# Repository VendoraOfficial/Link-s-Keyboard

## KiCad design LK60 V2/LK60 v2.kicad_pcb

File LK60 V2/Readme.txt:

LK60 V2 is a 60% keyboard with arduino pro micro as the microcontroller and use 2 mounting hole.

If u r wondering where is the v1. The project was gone into ashes, cause of my laptop got formated :')

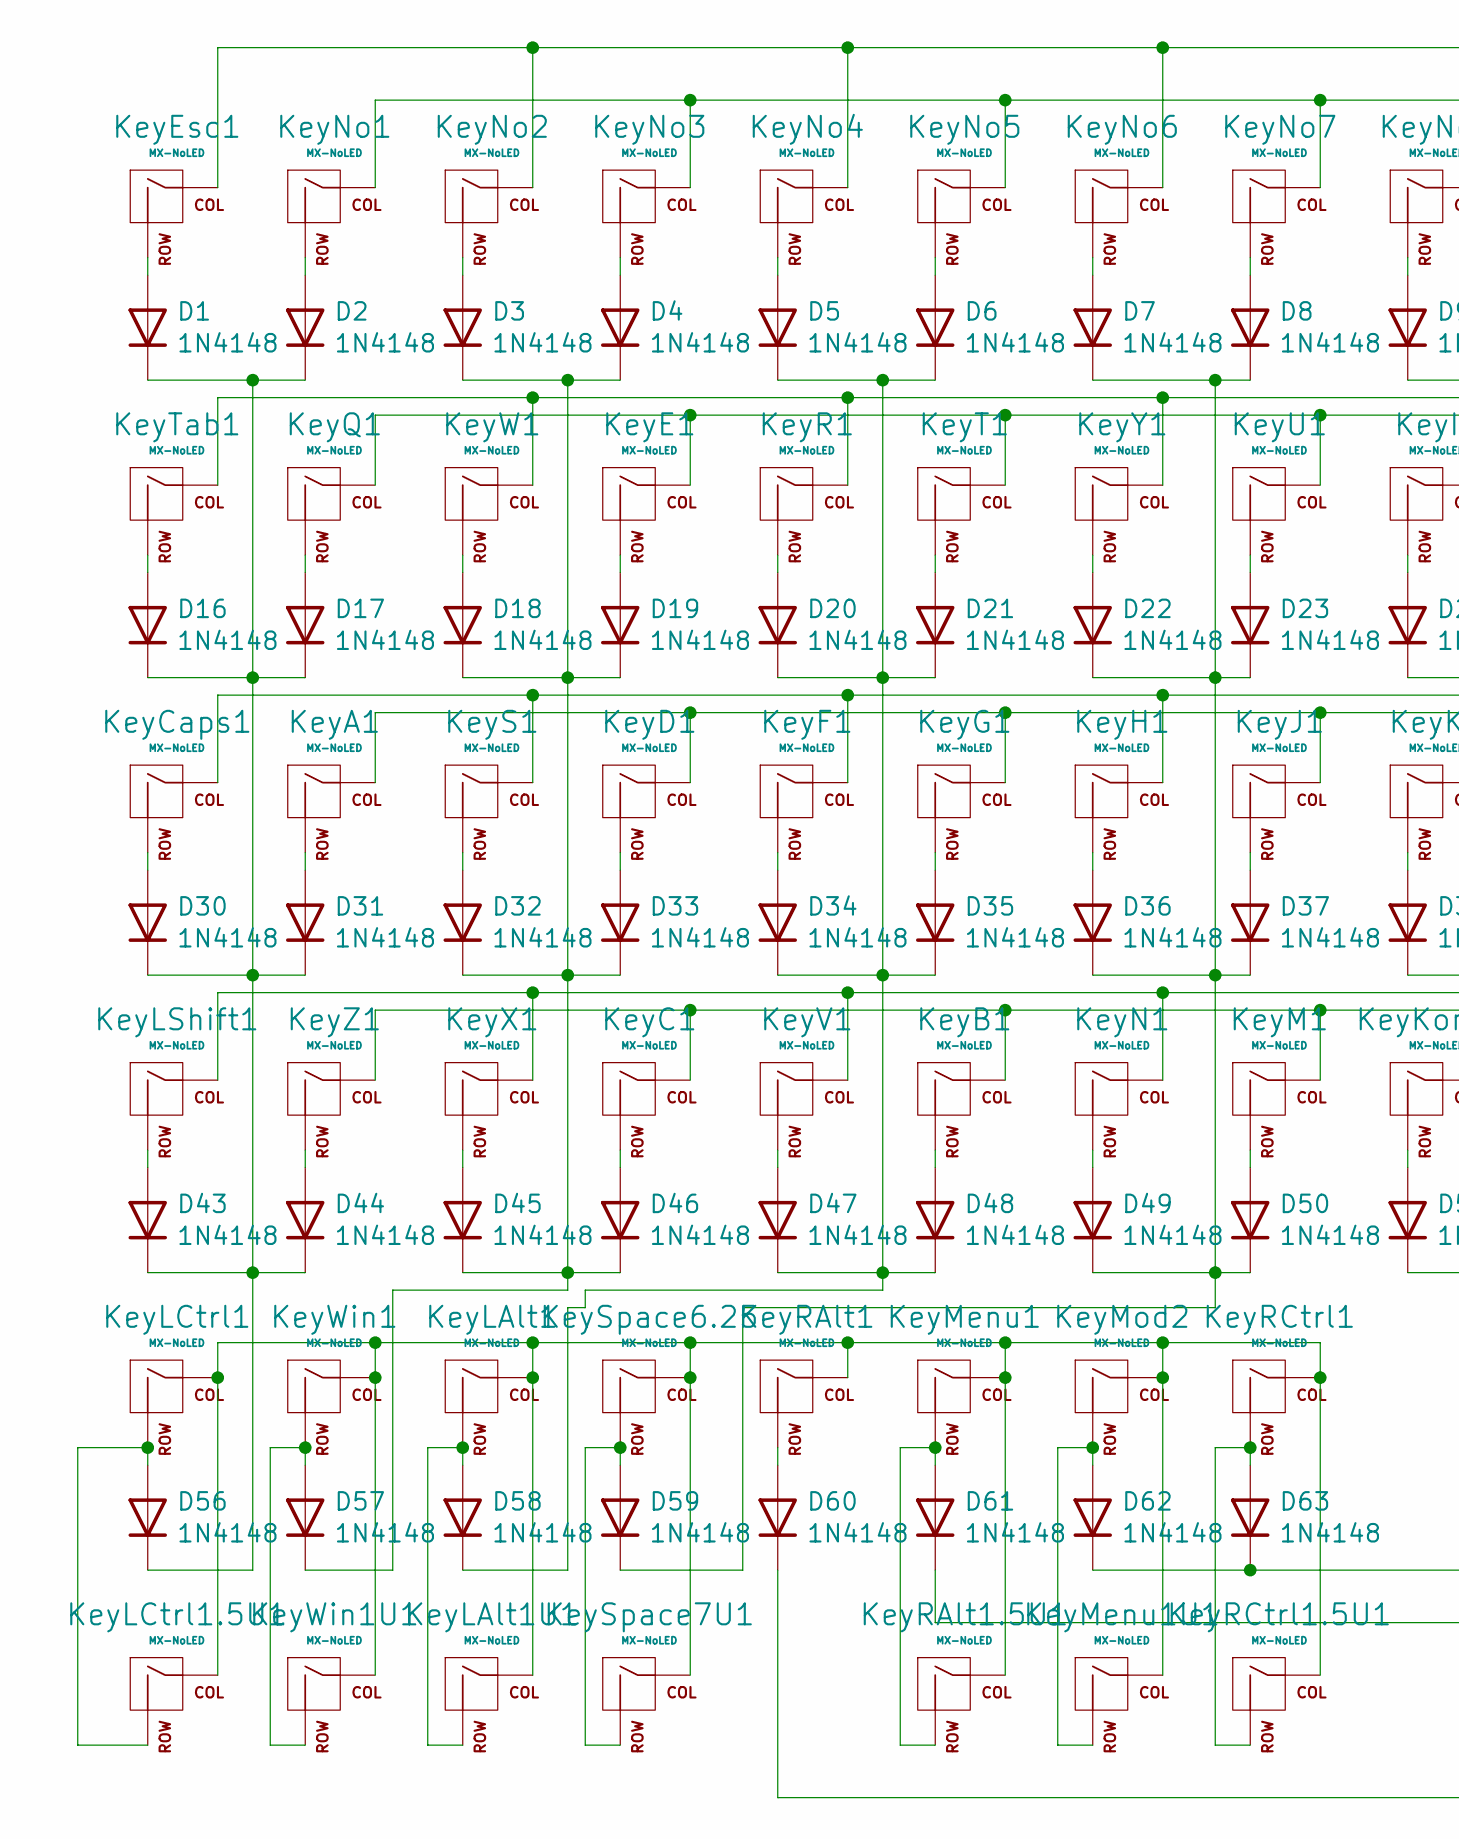
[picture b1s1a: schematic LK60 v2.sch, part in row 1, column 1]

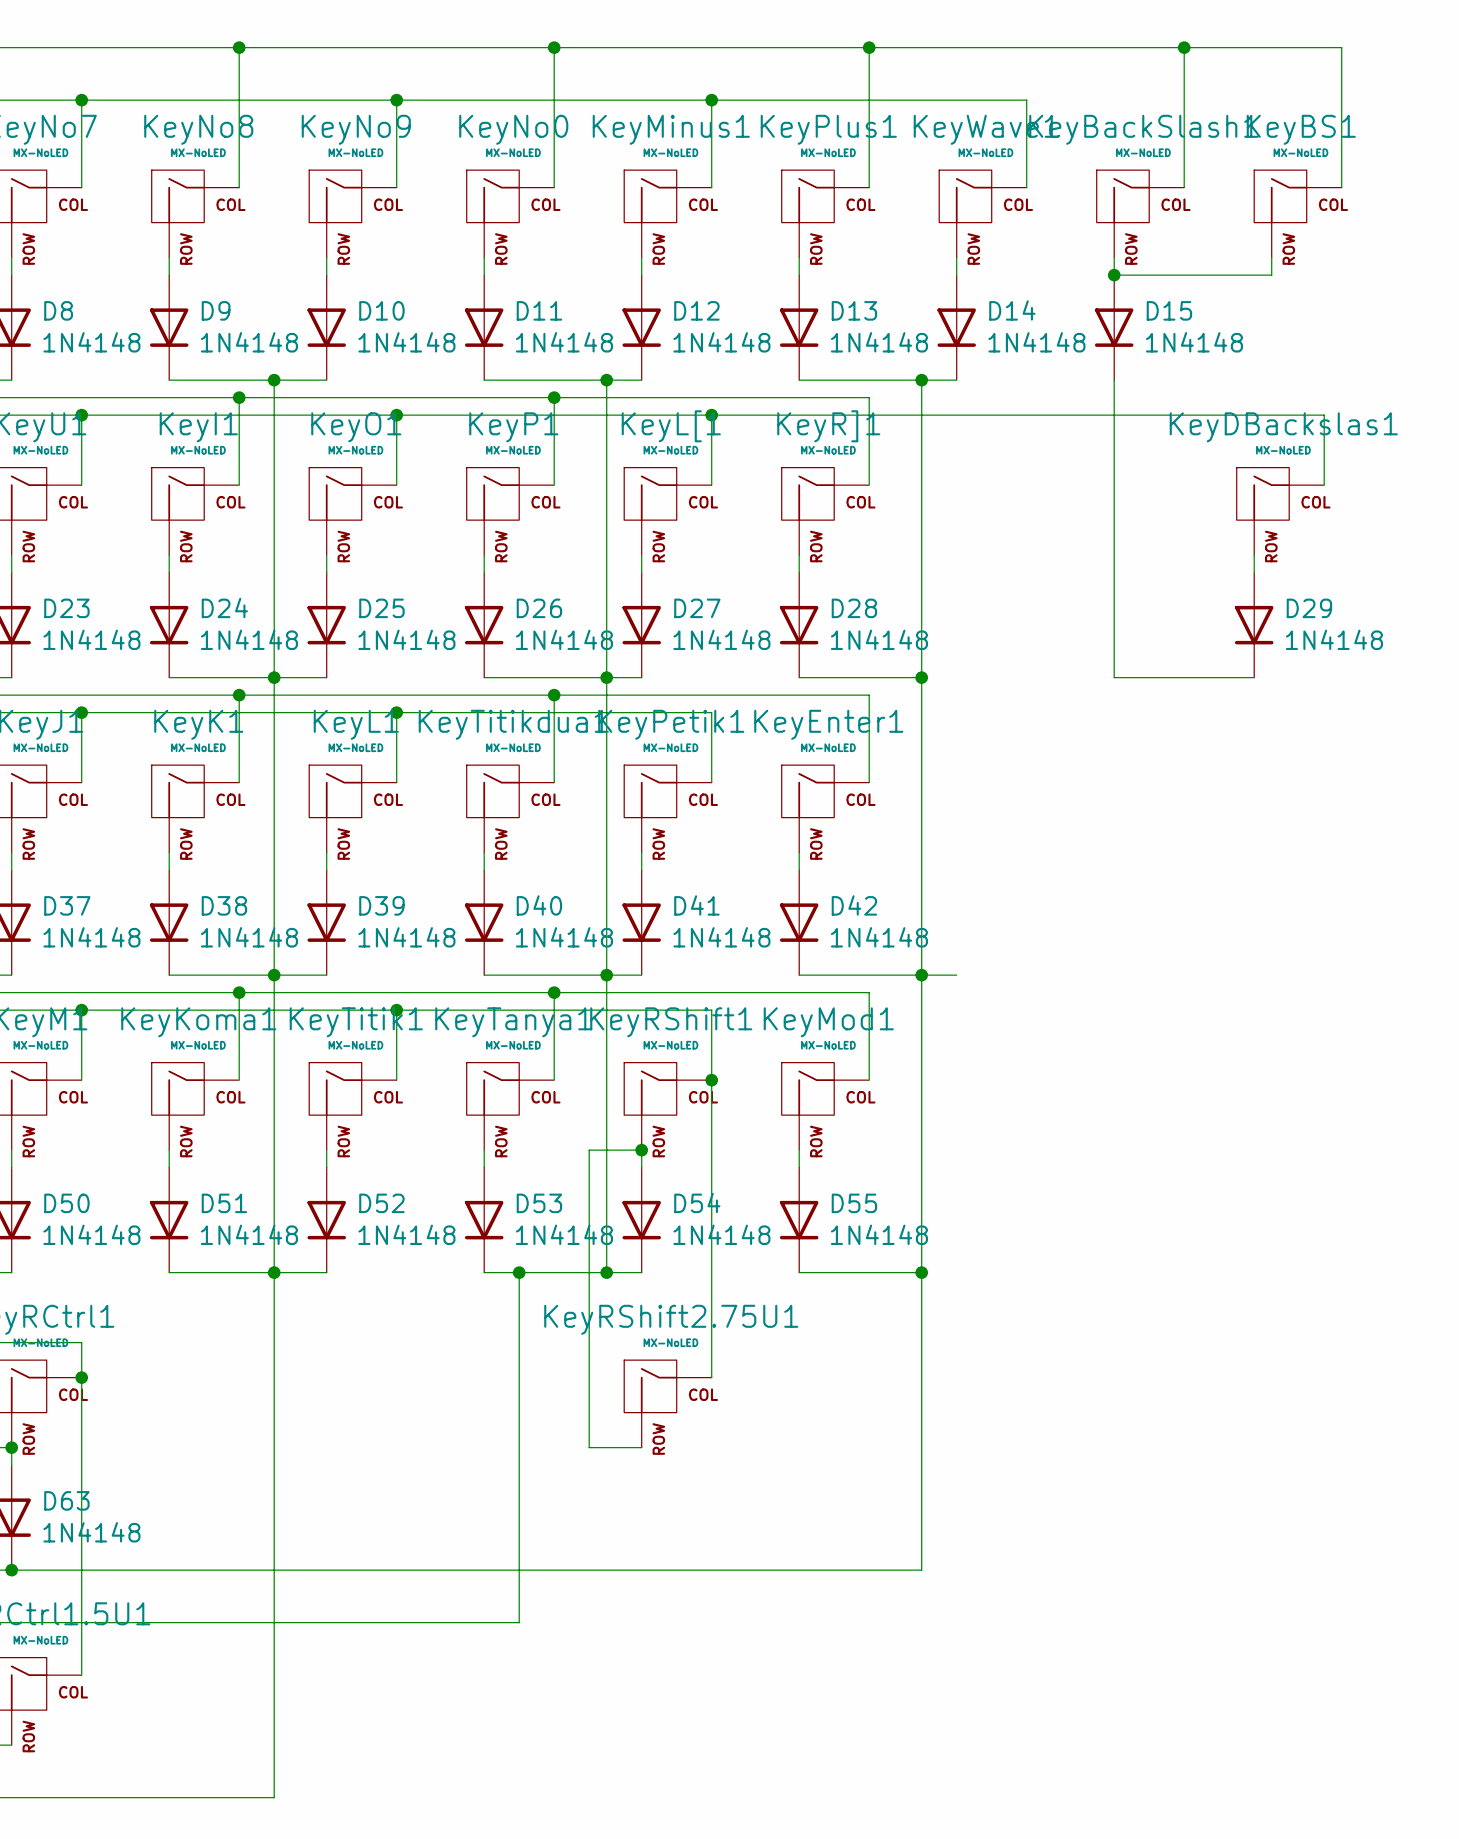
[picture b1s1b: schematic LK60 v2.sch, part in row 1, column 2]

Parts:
D1, D2, D3, D4, D5, D6, D7, D8, D9, D10, D11, D12, D13, D14, D15, D16, D17, D18, D19, D20, D21, D22, D23, D24, D25, D26, D27, D28, D29, D30, D31, D32, D33, D34, D35, D36, D37, D38, D39, D40, D41, D42, D43, D44, D45, D46, D47, D48, D49, D50, D51, D52, D53, D54, D55, D56, D57, D58, D59, D60, D61, D62, D63: 1N4148; D_DO-35_SOD27_P7.62mm_Horizontal
KeyA1: MX-NoLED; MXOnly-1U-NoLED
KeyB1: MX-NoLED; MXOnly-1U-NoLED
KeyBS1: MX-NoLED; MXOnly-2U-NoLED
KeyBackSlash1: MX-NoLED; MXOnly-1U-NoLED
KeyC1: MX-NoLED; MXOnly-1U-NoLED
KeyCaps1: MX-NoLED; MXOnly-1.75U-NoLED
KeyD1: MX-NoLED; MXOnly-1U-NoLED
KeyDBackslas1: MX-NoLED; MXOnly-1.5U-NoLED
KeyE1: MX-NoLED; MXOnly-1U-NoLED
KeyEnter1: MX-NoLED; MXOnly-2.25U-ReversedStabilizers-NoLED
KeyEsc1: MX-NoLED; MXOnly-1U-NoLED
KeyF1: MX-NoLED; MXOnly-1U-NoLED
KeyG1: MX-NoLED; MXOnly-1U-NoLED
KeyH1: MX-NoLED; MXOnly-1U-NoLED
KeyI1: MX-NoLED; MXOnly-1U-NoLED
KeyJ1: MX-NoLED; MXOnly-1U-NoLED
KeyK1: MX-NoLED; MXOnly-1U-NoLED
KeyKoma1: MX-NoLED; MXOnly-1U-NoLED
KeyL1: MX-NoLED; MXOnly-1U-NoLED
KeyLAlt1: MX-NoLED; MXOnly-1.25U-NoLED
KeyLAlt1U1: MX-NoLED; MXOnly-1.5U-NoLED
KeyLCtrl1: MX-NoLED; MXOnly-1.25U-NoLED
KeyLCtrl1.5U1: MX-NoLED; MXOnly-1.5U-NoLED
KeyLShift1: MX-NoLED; MXOnly-2.25U-NoLED
KeyL[1: MX-NoLED; MXOnly-1U-NoLED
KeyM1: MX-NoLED; MXOnly-1U-NoLED
KeyMenu1: MX-NoLED; MXOnly-1.25U-NoLED
KeyMenu1U1: MX-NoLED; MXOnly-1U-NoLED
KeyMinus1: MX-NoLED; MXOnly-1U-NoLED
KeyMod1: MX-NoLED; MXOnly-1U-NoLED
KeyMod2: MX-NoLED; MXOnly-1.25U-NoLED
KeyN1: MX-NoLED; MXOnly-1U-NoLED
KeyNo0, KeyNo1, KeyNo2, KeyNo3, KeyNo4, KeyNo5, KeyNo6, KeyNo7, KeyNo8, KeyNo9: MX-NoLED; MXOnly-1U-NoLED
KeyO1: MX-NoLED; MXOnly-1U-NoLED
KeyP1: MX-NoLED; MXOnly-1U-NoLED
KeyPetik1: MX-NoLED; MXOnly-1U-NoLED
KeyPlus1: MX-NoLED; MXOnly-1U-NoLED
KeyQ1: MX-NoLED; MXOnly-1U-NoLED
KeyR1: MX-NoLED; MXOnly-1U-NoLED
KeyRAlt1: MX-NoLED; MXOnly-1.25U-NoLED
KeyRAlt1.5U1: MX-NoLED; MXOnly-1.5U-NoLED
KeyRCtrl1: MX-NoLED; MXOnly-1.25U-NoLED
KeyRCtrl1.5U1: MX-NoLED; MXOnly-1.5U-NoLED
KeyRShift1: MX-NoLED; MXOnly-1.75U-NoLED
KeyRShift2.75U1: MX-NoLED; MXOnly-2.75U-NoLED
KeyR]1: MX-NoLED; MXOnly-1U-NoLED
KeyS1: MX-NoLED; MXOnly-1U-NoLED
KeySpace6.25: MX-NoLED; MXOnly-6.25U-ReversedStabilizers-NoLED
KeySpace7U1: MX-NoLED; MXOnly-7U-ReversedStabilizers-NoLED
KeyT1: MX-NoLED; MXOnly-1U-NoLED
KeyTab1: MX-NoLED; MXOnly-1.5U-NoLED
KeyTanya1: MX-NoLED; MXOnly-1U-NoLED
KeyTitik1: MX-NoLED; MXOnly-1U-NoLED
KeyTitikdua1: MX-NoLED; MXOnly-1U-NoLED
KeyU1: MX-NoLED; MXOnly-1U-NoLED
KeyV1: MX-NoLED; MXOnly-1U-NoLED
KeyW1: MX-NoLED; MXOnly-1U-NoLED
KeyWave1: MX-NoLED; MXOnly-1U-NoLED
KeyWin1: MX-NoLED; MXOnly-1.25U-NoLED
KeyWin1U1: MX-NoLED; MXOnly-1U-NoLED
KeyX1: MX-NoLED; MXOnly-1U-NoLED
KeyY1: MX-NoLED; MXOnly-1U-NoLED
KeyZ1: MX-NoLED; MXOnly-1U-NoLED

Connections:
Col0: KeyBS1.1 (COL), KeyBackSlash1.1 (COL), KeyEsc1.1 (COL), KeyNo0.1 (COL), KeyNo2.1 (COL), KeyNo4.1 (COL), KeyNo6.1 (COL), KeyNo8.1 (COL), KeyPlus1.1 (COL); also elsewhere on the board
Col1: KeyMinus1.1 (COL), KeyNo1.1 (COL), KeyNo3.1 (COL), KeyNo5.1 (COL), KeyNo7.1 (COL), KeyNo9.1 (COL), KeyWave1.1 (COL); also elsewhere on the board
Col2: KeyI1.1 (COL), KeyP1.1 (COL), KeyR1.1 (COL), KeyR]1.1 (COL), KeyTab1.1 (COL), KeyW1.1 (COL), KeyY1.1 (COL); also elsewhere on the board
Col3: KeyDBackslas1.1 (COL), KeyE1.1 (COL), KeyL[1.1 (COL), KeyO1.1 (COL), KeyQ1.1 (COL), KeyT1.1 (COL), KeyU1.1 (COL); also elsewhere on the board
Col4: KeyCaps1.1 (COL), KeyEnter1.1 (COL), KeyF1.1 (COL), KeyH1.1 (COL), KeyK1.1 (COL), KeyS1.1 (COL), KeyTitikdua1.1 (COL); also elsewhere on the board
Col5: KeyA1.1 (COL), KeyD1.1 (COL), KeyG1.1 (COL), KeyJ1.1 (COL), KeyL1.1 (COL), KeyPetik1.1 (COL); also elsewhere on the board
Col6: KeyKoma1.1 (COL), KeyLShift1.1 (COL), KeyMod1.1 (COL), KeyN1.1 (COL), KeyTanya1.1 (COL), KeyV1.1 (COL), KeyX1.1 (COL); also elsewhere on the board
Col7: KeyB1.1 (COL), KeyC1.1 (COL), KeyM1.1 (COL), KeyRShift1.1 (COL), KeyRShift2.75U1.1 (COL), KeyTitik1.1 (COL), KeyZ1.1 (COL); also elsewhere on the board
Col8: KeyLAlt1.1 (COL), KeyLAlt1U1.1 (COL), KeyLCtrl1.1 (COL), KeyLCtrl1.5U1.1 (COL), KeyMenu1.1 (COL), KeyMenu1U1.1 (COL), KeyMod2.1 (COL), KeyRAlt1.1 (COL), KeyRAlt1.5U1.1 (COL), KeyRCtrl1.1 (COL), KeyRCtrl1.5U1.1 (COL), KeySpace6.25.1 (COL), KeySpace7U1.1 (COL), KeyWin1.1 (COL), KeyWin1U1.1 (COL); also elsewhere on the board
unnamed: D1.2 (A), KeyEsc1.2 (ROW)
unnamed: D2.2 (A), KeyNo1.2 (ROW)
unnamed: D3.2 (A), KeyNo2.2 (ROW)
unnamed: D4.2 (A), KeyNo3.2 (ROW)
unnamed: D5.2 (A), KeyNo4.2 (ROW)
unnamed: D6.2 (A), KeyNo5.2 (ROW)
unnamed: D7.2 (A), KeyNo6.2 (ROW)
unnamed: D8.2 (A), KeyNo7.2 (ROW)
unnamed: D9.2 (A), KeyNo8.2 (ROW)
unnamed: D10.2 (A), KeyNo9.2 (ROW)
unnamed: D11.2 (A), KeyNo0.2 (ROW)
unnamed: D12.2 (A), KeyMinus1.2 (ROW)
unnamed: D13.2 (A), KeyPlus1.2 (ROW)
unnamed: D14.2 (A), KeyWave1.2 (ROW)
unnamed: D15.2 (A), KeyBS1.2 (ROW), KeyBackSlash1.2 (ROW)
unnamed: D16.2 (A), KeyTab1.2 (ROW)
unnamed: D17.2 (A), KeyQ1.2 (ROW)
unnamed: D18.2 (A), KeyW1.2 (ROW)
unnamed: D19.2 (A), KeyE1.2 (ROW)
unnamed: D20.2 (A), KeyR1.2 (ROW)
unnamed: D21.2 (A), KeyT1.2 (ROW)
unnamed: D22.2 (A), KeyY1.2 (ROW)
unnamed: D23.2 (A), KeyU1.2 (ROW)
unnamed: D24.2 (A), KeyI1.2 (ROW)
unnamed: D25.2 (A), KeyO1.2 (ROW)
unnamed: D26.2 (A), KeyP1.2 (ROW)
unnamed: D27.2 (A), KeyL[1.2 (ROW)
unnamed: D28.2 (A), KeyR]1.2 (ROW)
unnamed: D29.2 (A), KeyDBackslas1.2 (ROW)
unnamed: D30.2 (A), KeyCaps1.2 (ROW)
unnamed: D31.2 (A), KeyA1.2 (ROW)
unnamed: D32.2 (A), KeyS1.2 (ROW)
unnamed: D33.2 (A), KeyD1.2 (ROW)
unnamed: D34.2 (A), KeyF1.2 (ROW)
unnamed: D35.2 (A), KeyG1.2 (ROW)
unnamed: D36.2 (A), KeyH1.2 (ROW)
unnamed: D37.2 (A), KeyJ1.2 (ROW)
unnamed: D38.2 (A), KeyK1.2 (ROW)
unnamed: D39.2 (A), KeyL1.2 (ROW)
unnamed: D40.2 (A), KeyTitikdua1.2 (ROW)
unnamed: D41.2 (A), KeyPetik1.2 (ROW)
unnamed: D42.2 (A), KeyEnter1.2 (ROW)
unnamed: D43.2 (A), KeyLShift1.2 (ROW)
unnamed: D44.2 (A), KeyZ1.2 (ROW)
unnamed: D45.2 (A), KeyX1.2 (ROW)
unnamed: D46.2 (A), KeyC1.2 (ROW)
unnamed: D47.2 (A), KeyV1.2 (ROW)
unnamed: D48.2 (A), KeyB1.2 (ROW)
unnamed: D49.2 (A), KeyN1.2 (ROW)
unnamed: D50.2 (A), KeyM1.2 (ROW)
unnamed: D51.2 (A), KeyKoma1.2 (ROW)
unnamed: D52.2 (A), KeyTitik1.2 (ROW)
unnamed: D53.2 (A), KeyTanya1.2 (ROW)
unnamed: D54.2 (A), KeyRShift1.2 (ROW), KeyRShift2.75U1.2 (ROW)
unnamed: D55.2 (A), KeyMod1.2 (ROW)
unnamed: D56.2 (A), KeyLCtrl1.2 (ROW), KeyLCtrl1.5U1.2 (ROW)
unnamed: D57.2 (A), KeyWin1.2 (ROW), KeyWin1U1.2 (ROW)
unnamed: D58.2 (A), KeyLAlt1.2 (ROW), KeyLAlt1U1.2 (ROW)
unnamed: D59.2 (A), KeySpace6.25.2 (ROW), KeySpace7U1.2 (ROW)
unnamed: D60.2 (A), KeyRAlt1.2 (ROW)
unnamed: D61.2 (A), KeyMenu1.2 (ROW), KeyRAlt1.5U1.2 (ROW)
unnamed: D62.2 (A), KeyMenu1U1.2 (ROW), KeyMod2.2 (ROW)
unnamed: D63.2 (A), KeyRCtrl1.2 (ROW), KeyRCtrl1.5U1.2 (ROW)
Row0: D1.1 (K), D2.1 (K), D16.1 (K), D17.1 (K), D30.1 (K), D31.1 (K), D43.1 (K), D44.1 (K), D56.1 (K); also elsewhere on the board
Row1: D3.1 (K), D4.1 (K), D18.1 (K), D19.1 (K), D32.1 (K), D33.1 (K), D45.1 (K), D46.1 (K), D57.1 (K); also elsewhere on the board
Row2: D5.1 (K), D6.1 (K), D20.1 (K), D21.1 (K), D34.1 (K), D35.1 (K), D47.1 (K), D48.1 (K), D58.1 (K); also elsewhere on the board
Row3: D7.1 (K), D8.1 (K), D22.1 (K), D23.1 (K), D36.1 (K), D37.1 (K), D49.1 (K), D50.1 (K), D59.1 (K); also elsewhere on the board
Row4: D9.1 (K), D10.1 (K), D24.1 (K), D25.1 (K), D38.1 (K), D39.1 (K), D51.1 (K), D52.1 (K), D60.1 (K); also elsewhere on the board
Row5: D11.1 (K), D12.1 (K), D26.1 (K), D27.1 (K), D40.1 (K), D41.1 (K), D53.1 (K), D54.1 (K), D61.1 (K); also elsewhere on the board
Row6: D13.1 (K), D14.1 (K), D28.1 (K), D42.1 (K), D55.1 (K), D62.1 (K), D63.1 (K); also elsewhere on the board
Row7: D15.1 (K), D29.1 (K); also elsewhere on the board

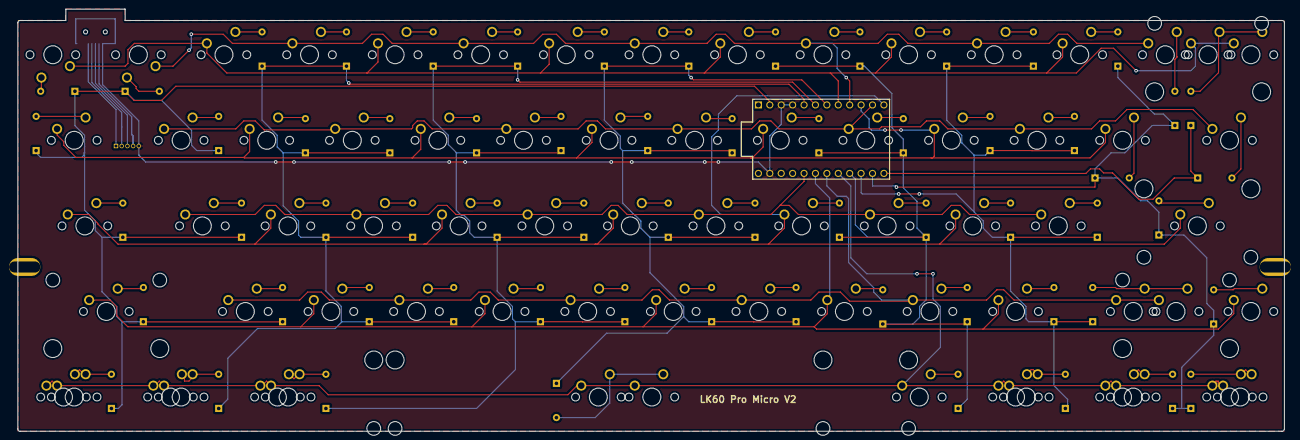
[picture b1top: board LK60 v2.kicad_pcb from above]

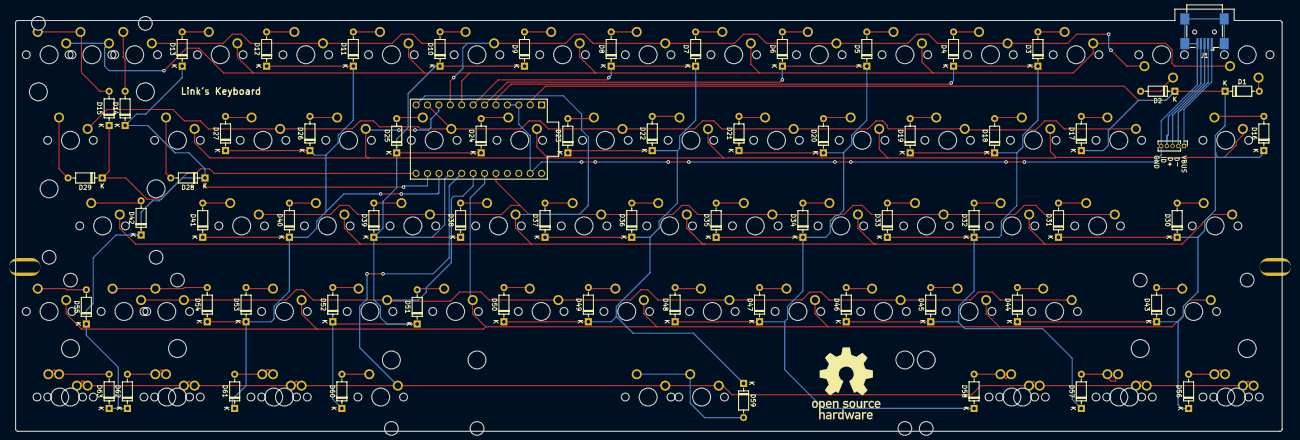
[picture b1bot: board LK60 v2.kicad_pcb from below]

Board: 2 copper layers, 281.9 x 94.0 mm, 138 parts (66 on the bottom side), 85 nets.

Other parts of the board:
J1: USB_B_Mini; USB_Mini-B_Wuerth_65100516121_Horizontal
Pin_header1: Conn_01x05; PinHeader_1x05_P1.27mm_Vertical
U1: ProMicro

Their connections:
Col0: U1.8; also elsewhere on the board
Col1: U1.9; also elsewhere on the board
Col2: U1.10; also elsewhere on the board
Col3: U1.11; also elsewhere on the board
Col4: U1.12; also elsewhere on the board
Col5: U1.20; also elsewhere on the board
Col6: U1.19; also elsewhere on the board
Col7: U1.18; also elsewhere on the board
Col8: U1.17; also elsewhere on the board
Ground: J1.5, J1.6, Pin_header1.5, U1.3, U1.4, U1.23
unnamed: J1.1, Pin_header1.1
unnamed: J1.2, Pin_header1.2
unnamed: J1.3, Pin_header1.3
unnamed: J1.4, Pin_header1.4
Row0: U1.2; also elsewhere on the board
Row1: U1.5; also elsewhere on the board
Row2: U1.6; also elsewhere on the board
Row3: U1.7; also elsewhere on the board
Row4: U1.16; also elsewhere on the board
Row5: U1.15; also elsewhere on the board
Row6: U1.14; also elsewhere on the board
Row7: U1.13; also elsewhere on the board
